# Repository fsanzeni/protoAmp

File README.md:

# 100W USB-C PD Audio Amplifier with Integrated DSP

This repository contains the hardware design files, documentation, and firmware logic for a 100W audio amplifier board. The system integrates USB-C Power Delivery (PD) for power management, a dedicated digital signal processor (DSP) for audio manipulation, a Bluetooth Low Energy (BLE) microcontroller for system management, and a high-efficiency Class-D amplification stage.

This platform is designed for active speaker systems, custom crossover networks, and integrated audio processing applications requiring a compact footprint and standardised power inputs.

| PCB Front | PCB Back |
|-----------|----------|
|  |  |

---

## System Architecture and Major Components

The board design relies on a specialised set of integrated circuits to handle power negotiation, wireless connectivity, digital signal processing, and audio amplification.

### USB Power Delivery: HUSB238

The [HUSB238](https://en.hynetek.com/2421.html) serves as the USB Type-C PD sink controller. It handles the low-level negotiation with the connected USB-C power source to request the necessary voltage and current (up to 20V at 5A, yielding 100W).

* **Protocol:** Compliant with USB PD 3.0 and Type-C 1.4 specifications.
* **Interface:** Interfaced via I2C, allowing the system MCU to read negotiated power capabilities and dynamically limit the amplifier's maximum output power to prevent source overcurrent.
* **Functionality:** Operates independently of the MCU for fundamental power requests, ensuring rapid voltage ramp-up and system stability upon cable insertion. Please note: without writing some code and pushing it via the exposed I2C lines, the HUSB238 can only output a maximum of 20V @ 3A (60W). This is a safety feature. Please see e.g., [Adafruit's](https://github.com/adafruit/Adafruit_HUSB238) code to figure out how to request up to 100W.

### Digital Signal Processor: ADAU1701

Audio processing is handled by the Analog Devices [ADAU1701](https://www.analog.com/en/products/adau1701.html), a fully programmable 28-/56-bit audio DSP.

* **Processing:** Executes audio algorithms at a high sample rate, suitable for bi-quad filters, dynamic range compression, time alignment, and active crossovers.
* **I/O Routing:** Features two built-in ADCs and four DACs, allowing for stereo input and up to four channels of analog output (e.g., routing separate high-frequency and low-frequency channels to the amplification stage).
* **Programming:** Configurable via Analog Devices' SigmaStudio. The DSP boots from an external EEPROM or is initialised via the I2C bus by the system MCU.

### System Controller & Wireless: STM32WBA65

The STMicroelectronics [STM32WBA65CIU6](https://www.st.com/en/microcontrollers-microprocessors/stm32wba65ci.html) acts as the central brain of the board. It is an ultra-low-power Arm Cortex-M33 microcontroller with integrated Bluetooth LE Audio capabilities.

* **System Management:** Acts as the I2C master to configure the HUSB238 (via solder jumpers) and the ADAU1701 (loading DSP parameters or switching presets).
* **Connectivity:** Handles Bluetooth Low Energy (BLE) connections for audio streaming and remote configuration, effectively acting as the bridge between mobile applications and the onboard DSP.

### Audio Amplification Stage

The output stage uses a Class-D amplifier topology configured to deliver up to 100W of total output power, distributed as either a bridged mono (PBTL) output or a standard stereo configuration - or a combination of both.

I'm using here a pair of synced [TPA3126D2DADR](https://www.ti.com/product/TPA3126D2/part-details/TPA3126D2DADR) - one configured as a 50-W stereo amp, the second as a 100-W amp. Obviously you can't request their max wattage at the same time, so I've included a PLIMIT circuit for both. You can also limit the individual amp's power limits via the DSP / SigmaStudio, but better safe than sorry!

---

## License

This project is licensed under the MIT License.

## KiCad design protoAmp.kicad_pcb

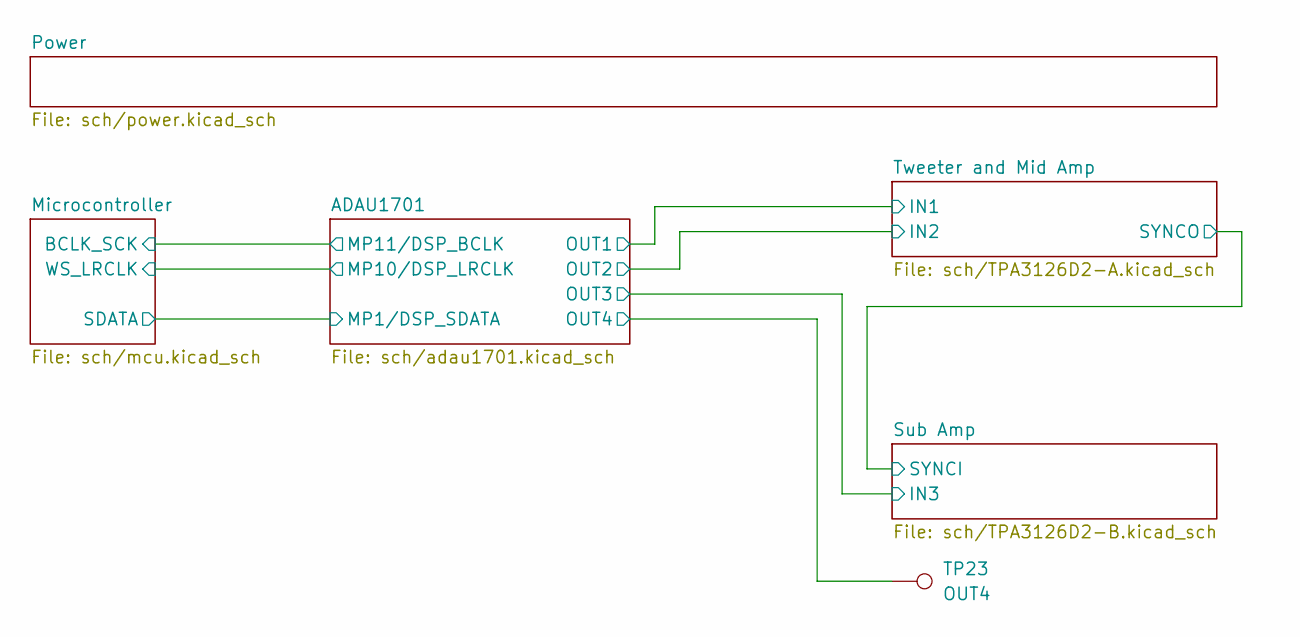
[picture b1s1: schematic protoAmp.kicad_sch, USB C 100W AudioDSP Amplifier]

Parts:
TP23: OUT4; TestPoint_Pad_1.0x1.0mm

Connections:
/ADAU1701/OUT4: TP23.1 (1_1); also elsewhere on the board

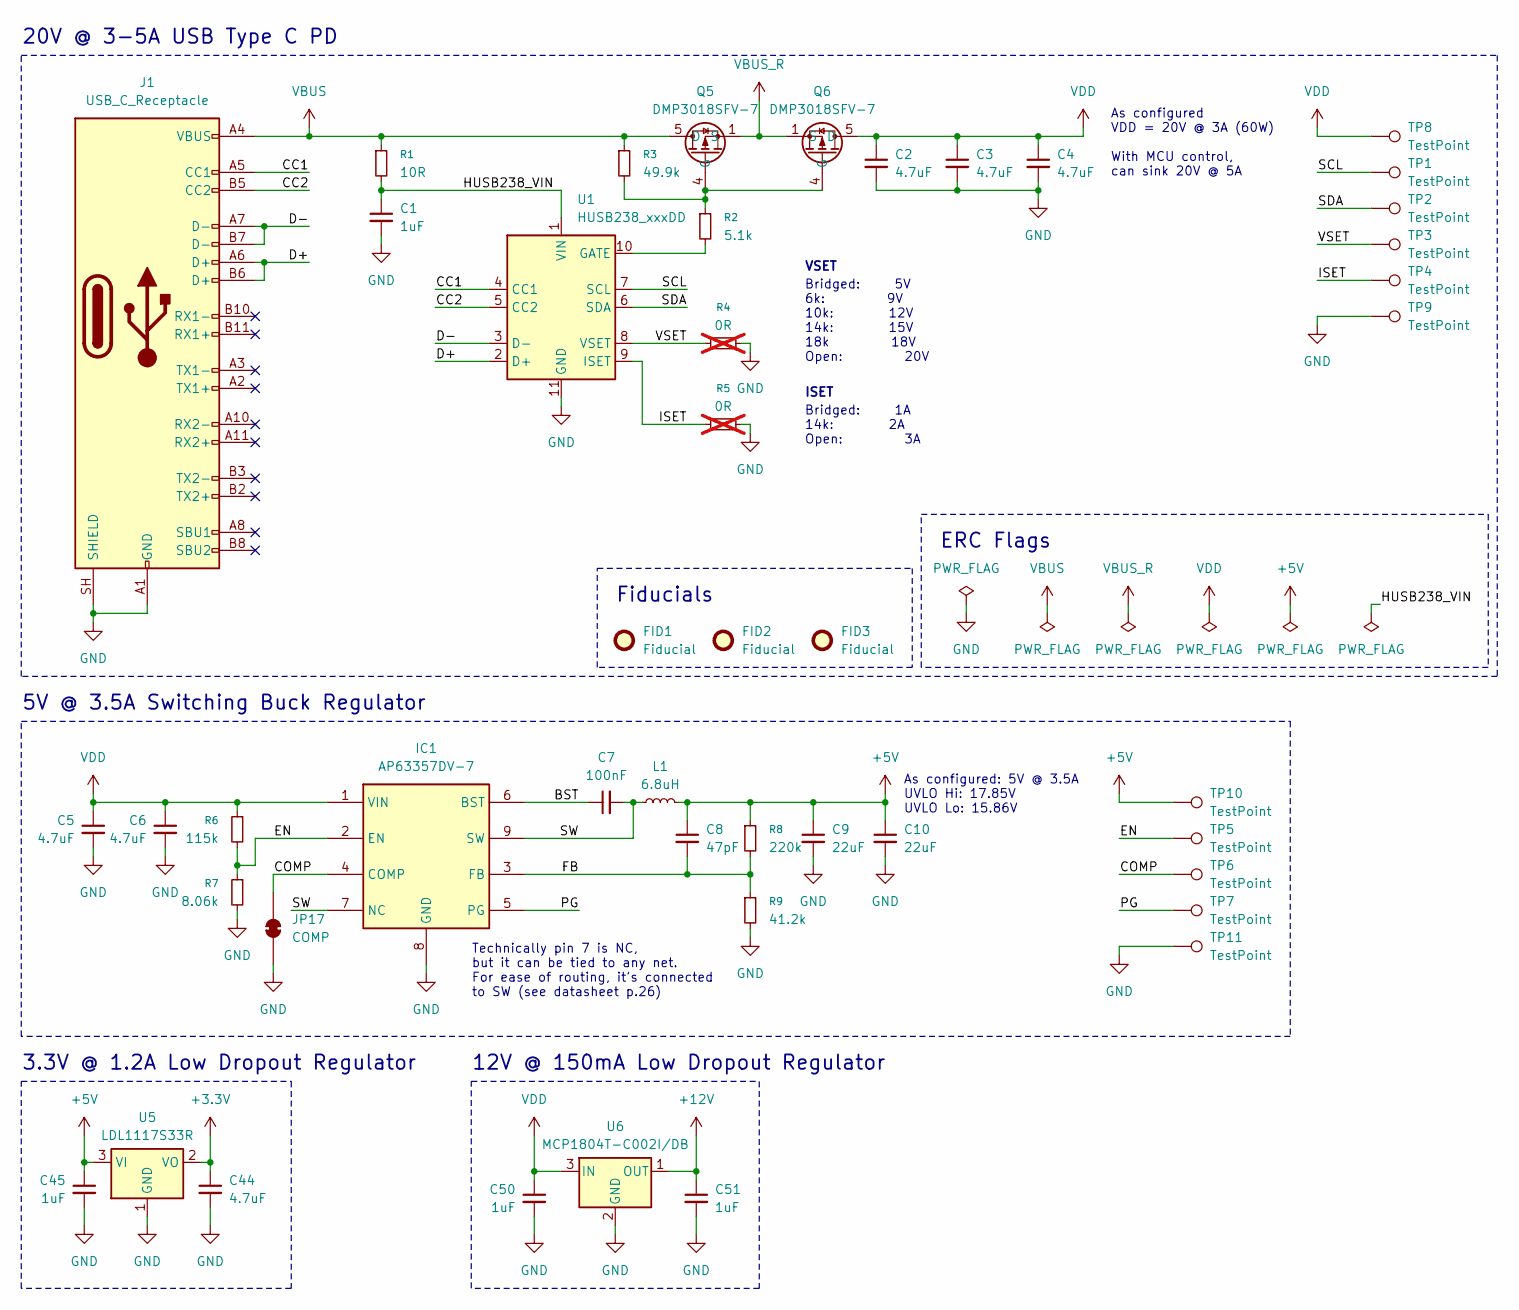
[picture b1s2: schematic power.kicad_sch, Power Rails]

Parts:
C1, C45, C50, C51: 1uF; C_0805_2012Metric
C2, C3, C4, C5, C6, C44: 4.7uF; C_0805_2012Metric
C7: 100nF; C_0402_1005Metric
C8: 47pF; C_0402_1005Metric
C9, C10: 22uF; C_0805_2012Metric
FID1, FID2, FID3: Fiducial; Fiducial_0.75mm_Mask1.5mm
IC1: AP63357DV-7; AP63357DV7; Mouser Part Number 621-AP63357DV-7
J1: USB_C_Receptacle; USB4900-00-A
JP17: COMP; SolderJumper-2_P1.3mm_Bridged_RoundedPad1.0x1.5mm
L1: 6.8uH; SRP1265A-100M
Q5, Q6: DMP3018SFV-7; DMP3036SFV7; Mouser Part Number 621-DMP3018SFV-7
R1: 10R; R_0603_1608Metric
R2: 5.1k; R_0603_1608Metric
R3: 49.9k; R_0603_1608Metric
R4, R5: 0R; R_0603_1608Metric; not fitted
R6: 115k; R_0402_1005Metric
R7: 8.06k; R_0402_1005Metric
R8: 220k; R_0402_1005Metric
R9: 41.2k; R_0402_1005Metric
TP1, TP2, TP3, TP4, TP5, TP6, TP7, TP8, TP9, TP10, TP11: TestPoint; TestPoint_Pad_1.0x1.0mm
U1: HUSB238_xxxDD; WDFN-10-1EP_3x3mm_P0.5mm_EP1.8x2.5mm
U5: LDL1117S33R; SOT-223-3_TabPin2
U6: MCP1804T-C002I/DB; SOT-223-3_TabPin2

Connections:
+3.3V: C44.1, U5.2 (VO); also elsewhere on the board
+5V: C8.1, C9.1, C10.1, C45.1, L1.2, R8.1, TP10.1 (1_1), U5.3 (VI); also elsewhere on the board
+12V: C51.1, U6.1 (OUT); also elsewhere on the board
/Power/BST: C7.1, IC1.6 (BST)
/Power/CC1: J1.A5 (CC1), U1.4 (CC1)
/Power/CC2: J1.B5 (CC2), U1.5 (CC2)
/Power/COMP: IC1.4 (COMP), JP17.1 (A), TP6.1 (1_1)
/Power/D+: J1.A6 (D+), J1.B6 (D+), U1.2 (D+)
/Power/D-: J1.A7 (D-), J1.B7 (D-), U1.3 (D-)
/Power/EN: IC1.2 (EN), R6.2, R7.1, TP5.1 (1_1)
/Power/FB: C8.2, IC1.3 (FB), R8.2, R9.1
/Power/HUSB238_VIN: C1.1, R1.2, U1.1 (VIN)
/Power/ISET: R5.1, TP4.1 (1_1), U1.9 (ISET)
/Power/PG: IC1.5 (PG), TP7.1 (1_1)
/Power/SCL: TP1.1 (1_1), U1.7 (SCL)
/Power/SDA: TP2.1 (1_1), U1.6 (SDA)
/Power/SW: C7.2, IC1.7 (NC), IC1.9 (SW), L1.1
/Power/VSET: R4.1, TP3.1 (1_1), U1.8 (VSET)
GND: C1.2, C2.2, C3.2, C4.2, C5.2, C6.2, C9.2, C10.2, C44.2, C45.2, C50.2, C51.2, IC1.8 (GND), J1.A1 (GND), J1.A12 (GND), J1.B1 (GND), J1.B12 (GND), J1.SH (SHIELD), JP17.2 (B), R4.2, R5.2, R7.2, R9.2, TP9.1 (1_1), TP11.1 (1_1), U1.11 (GND), U5.1 (GND), U6.2 (GND); also elsewhere on the board
unnamed: Q5.4 (G), Q6.4 (G), R2.1, R3.2
unnamed: R2.2, U1.10 (GATE)
VBUS: J1.A4 (VBUS), J1.A9 (VBUS), J1.B4 (VBUS), J1.B9 (VBUS), Q5.5 (D), Q5.6 (D), Q5.7 (D), Q5.8 (D), Q5.9 (D), R1.1, R3.1
VBUS_R: Q5.1 (S), Q5.2 (S), Q5.3 (S), Q6.1 (S), Q6.2 (S), Q6.3 (S)
VDD: C2.1, C3.1, C4.1, C5.1, C6.1, C50.1, IC1.1 (VIN), Q6.5 (D), Q6.6 (D), Q6.7 (D), Q6.8 (D), Q6.9 (D), R6.1, TP8.1 (1_1), U6.3 (IN); also elsewhere on the board

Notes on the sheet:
3.3V @ 1.2A Low Dropout Regulator
Bridged: 1A 14k: 2A Open: 3A
As configured: 5V @ 3.5A UVLO Hi: 17.85V UVLO Lo: 15.86V
Technically pin 7 is NC, but it can be tied to any net. For ease of routing, it's connected to SW (see datasheet p.26)
20V @ 3-5A USB Type C PD
As configured VDD = 20V @ 3A (60W) With MCU control, can sink 20V @ 5A
Fiducials
5V @ 3.5A Switching Buck Regulator
12V @ 150mA Low Dropout Regulator
VSET
Bridged: 5V 6k: 9V 10k: 12V 14k: 15V 18k 18V Open: 20V
ERC Flags
ISET

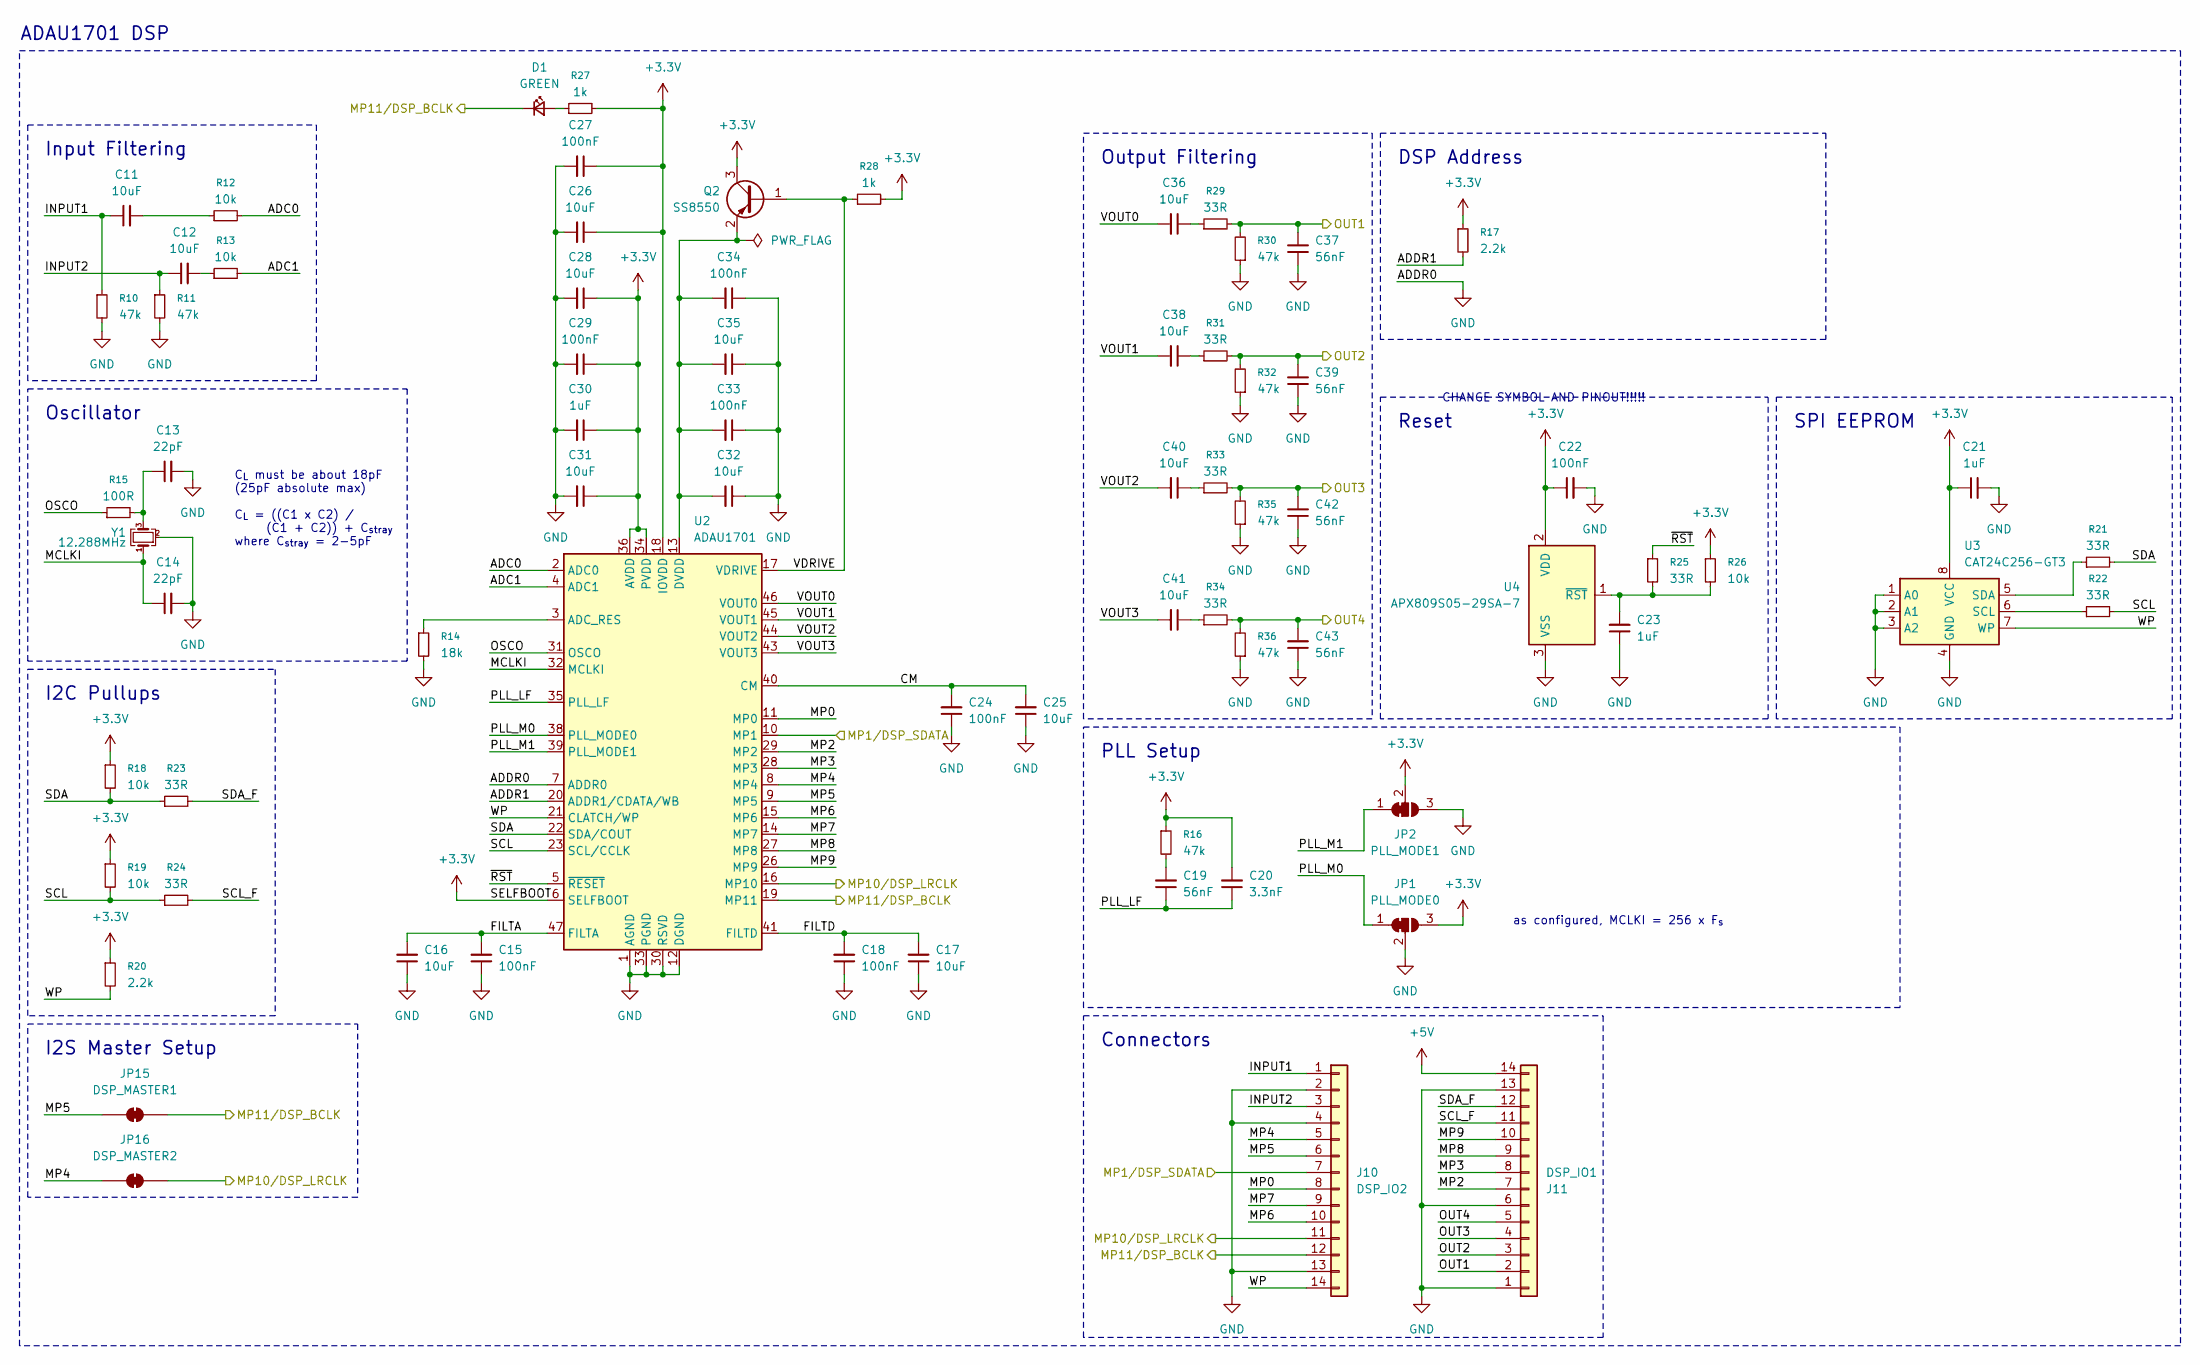
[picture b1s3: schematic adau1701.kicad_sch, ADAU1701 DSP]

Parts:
C11, C12, C16, C17, C25, C26, C28, C31, C32, C35, C36, C38, C40, C41: 10uF; C_0805_2012Metric
C13, C14: 22pF; C_0402_1005Metric
C15, C18, C22, C24, C27, C29, C33, C34: 100nF; C_0402_1005Metric
C19, C37, C39, C42, C43: 56nF; C_0402_1005Metric
C20: 3.3nF; C_0402_1005Metric
C21, C23, C30: 1uF; C_0805_2012Metric
D1: GREEN; LED_0603_1608Metric
J10: DSP_IO2; PinHeader_1x14_P2.54mm_Vertical
J11: DSP_IO1; PinHeader_1x14_P2.54mm_Vertical
JP1: PLL_MODE0; SolderJumper-3_P1.3mm_Bridged12_Pad1.0x1.5mm
JP2: PLL_MODE1; SolderJumper-3_P1.3mm_Bridged12_Pad1.0x1.5mm
JP15: DSP_MASTER1; SolderJumper-2_P1.3mm_Bridged_RoundedPad1.0x1.5mm
JP16: DSP_MASTER2; SolderJumper-2_P1.3mm_Bridged_RoundedPad1.0x1.5mm
Q2: SS8550; SOT-23
R10, R11, R16, R30, R32, R35, R36: 47k; R_0402_1005Metric
R12, R13, R18, R19, R26: 10k; R_0402_1005Metric
R14: 18k; R_0402_1005Metric
R15: 100R; R_0402_1005Metric
R17, R20: 2.2k; R_0402_1005Metric
R21, R22, R23, R24, R25, R29, R31, R33, R34: 33R; R_0402_1005Metric
R27, R28: 1k; R_0402_1005Metric
U2: ADAU1701; LQFP-48_7x7mm_P0.5mm
U3: CAT24C256-GT3; TSSOP-8_4.4x3mm_P0.65mm
U4: APX809S05-29SA-7; SOT-23-3
Y1: 12.288MHz; XTM32012288JT00351001

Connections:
+3.3V: C20.2, C21.1, C22.1, C26.1, C27.1, C28.1, C29.1, C30.1, C31.1, JP1.3 (B), JP2.2 (C), Q2.3 (C), R16.1, R17.1, R18.1, R19.1, R20.1, R26.1, R27.2, R28.2, U2.6 (SELFBOOT), U2.18 (IOVDD), U2.34 (PVDD), U2.36 (AVDD), U2.48 (AVDD), U3.8 (VCC), U4.2 (VDD); also elsewhere on the board
+5V: J11.14; also elsewhere on the board
/ADAU1701/ADC0: R12.2, U2.2 (ADC0)
/ADAU1701/ADC1: R13.2, U2.4 (ADC1)
/ADAU1701/ADDR1: R17.2, U2.20 (ADDR1/CDATA/WB)
/ADAU1701/CM: C24.2, C25.2, U2.40 (CM)
/ADAU1701/FILTA: C15.2, C16.2, U2.47 (FILTA)
/ADAU1701/FILTD: C17.2, C18.2, U2.41 (FILTD)
/ADAU1701/INPUT1: C11.1, J10.1, R10.1
/ADAU1701/INPUT2: C12.1, J10.3, R11.1
/ADAU1701/MCLKI: C14.1, U2.32 (MCLKI), Y1.1
/ADAU1701/MP0: J10.8, U2.11 (MP0)
/ADAU1701/MP1/DSP_SDATA: J10.7, U2.10 (MP1); also elsewhere on the board
/ADAU1701/MP2: J11.7, U2.29 (MP2)
/ADAU1701/MP3: J11.8, U2.28 (MP3)
/ADAU1701/MP4: J10.5, JP16.2 (B), U2.8 (MP4)
/ADAU1701/MP5: J10.6, JP15.2 (B), U2.9 (MP5)
/ADAU1701/MP6: J10.10, U2.15 (MP6)
/ADAU1701/MP7: J10.9, U2.14 (MP7)
/ADAU1701/MP8: J11.9, U2.27 (MP8)
/ADAU1701/MP9: J11.10, U2.26 (MP9)
/ADAU1701/MP10/DSP_LRCLK: J10.11, JP16.1 (A), U2.16 (MP10); also elsewhere on the board
/ADAU1701/MP11/DSP_BCLK: D1.1 (K), J10.12, JP15.1 (A), U2.19 (MP11); also elsewhere on the board
/ADAU1701/OSCO: R15.1, U2.31 (OSCO)
/ADAU1701/OUT1: C37.2, J11.2, R29.2, R30.2; also elsewhere on the board
/ADAU1701/OUT2: C39.2, J11.3, R31.2, R32.2; also elsewhere on the board
/ADAU1701/OUT3: C42.2, J11.4, R33.2, R35.2; also elsewhere on the board
/ADAU1701/OUT4: C43.2, J11.5, R34.2, R36.2; also elsewhere on the board
/ADAU1701/PLL_LF: C19.1, C20.1, U2.35 (PLL_LF)
/ADAU1701/PLL_M0: JP1.1 (A), U2.38 (PLL_MODE0)
/ADAU1701/PLL_M1: JP2.1 (A), U2.39 (PLL_MODE1)
/ADAU1701/SCL: R19.2, R22.2, R24.1, U2.23 (SCL/CCLK)
/ADAU1701/SCL_F: J11.11, R24.2
/ADAU1701/SDA: R18.2, R21.2, R23.1, U2.22 (SDA/COUT)
/ADAU1701/SDA_F: J11.12, R23.2
/ADAU1701/VDRIVE: Q2.1 (B), R28.1, U2.17 (VDRIVE)
/ADAU1701/VOUT0: C36.2, U2.46 (VOUT0)
/ADAU1701/VOUT1: C38.2, U2.45 (VOUT1)
/ADAU1701/VOUT2: C40.2, U2.44 (VOUT2)
/ADAU1701/VOUT3: C41.2, U2.43 (VOUT3)
/ADAU1701/WP: J10.14, R20.2, U2.21 (CLATCH/WP), U3.7 (WP)
/ADAU1701/~RST: R25.1, U2.5 (~RESET)
GND: C13.2, C14.2, C15.1, C16.1, C17.1, C18.1, C21.2, C22.2, C23.1, C24.1, C25.1, C26.2, C27.2, C28.2, C29.2, C30.2, C31.2, C32.1, C33.1, C34.1, C35.1, C37.1, C39.1, C42.1, C43.1, J10.2, J10.4, J10.13, J11.1, J11.6, J11.13, JP1.2 (C), JP2.3 (B), R10.2, R11.2, R14.2, R30.1, R32.1, R35.1, R36.1, U2.1 (AGND), U2.7 (ADDR0), U2.12 (DGND), U2.25 (DGND), U2.30 (RSVD), U2.33 (PGND), U2.37 (AGND), U2.42 (AGND), U3.1 (A0), U3.2 (A1), U3.3 (A2), U3.4 (GND), U4.3 (VSS), Y1.2 (G), Y1.4 (G); also elsewhere on the board
unnamed: C11.2, R12.1
unnamed: C12.2, R13.1
unnamed: C13.1, R15.2, Y1.3
unnamed: C19.2, R16.2
unnamed: C36.1, R29.1
unnamed: C38.1, R31.1
unnamed: C40.1, R33.1
unnamed: C41.1, R34.1
unnamed: D1.2 (A), R27.1
unnamed: C32.2, C33.2, C34.2, C35.2, Q2.2 (E), U2.13 (DVDD), U2.24 (DVDD)
unnamed: R14.1, U2.3 (ADC_RES)
unnamed: R22.1, U3.6 (SCL)
unnamed: R21.1, U3.5 (SDA)
unnamed: C23.2, R25.2, R26.2, U4.1 (~RST)

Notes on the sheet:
Reset
C_{L} must be about 18pF (25pF absolute max) C_{L} = ((C1 x C2) / (C1 + C2)) + C_{stray} where C_{stray} = 2-5pF
Output Filtering
PLL Setup
ADAU1701 DSP
Input Filtering
I2S Master Setup
SPI EEPROM
Oscillator
I2C Pullups
as configured, MCLKI = 256 x F_{s}
DSP Address
CHANGE SYMBOL AND PINOUT!!!!!
Connectors

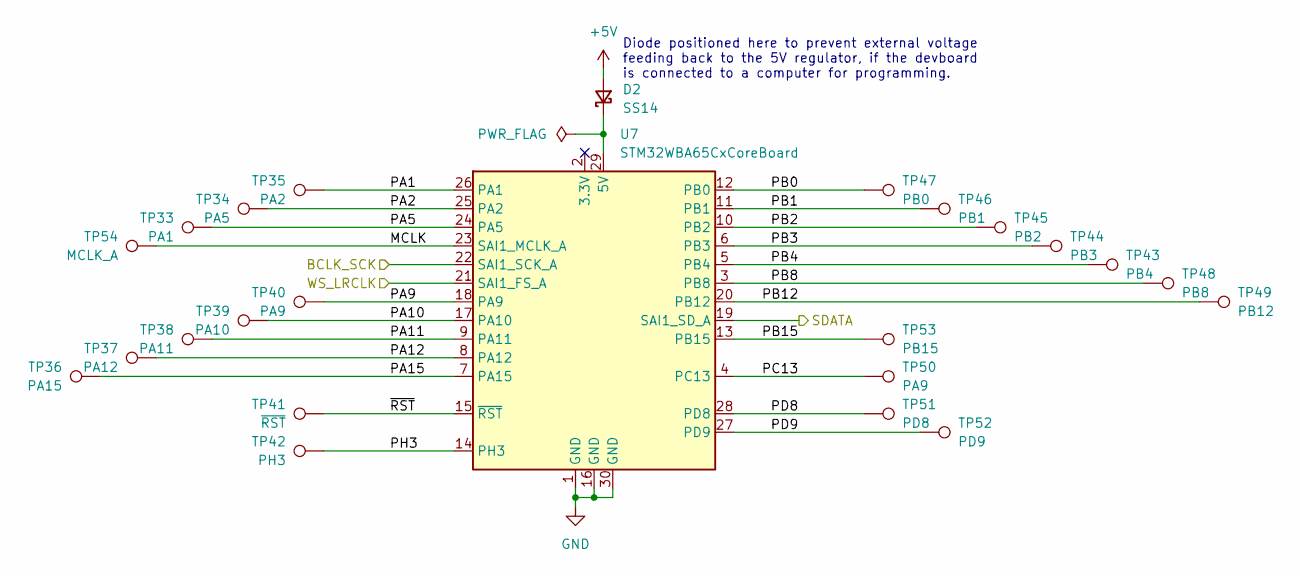
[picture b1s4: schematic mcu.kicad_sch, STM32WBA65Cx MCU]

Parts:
D2: SS14; D_SMA
TP33: PA1; TestPoint_THTPad_1.0x1.0mm_Drill0.5mm
TP34: PA5; TestPoint_THTPad_1.0x1.0mm_Drill0.5mm
TP35: PA2; TestPoint_THTPad_1.0x1.0mm_Drill0.5mm
TP36: PA15; TestPoint_THTPad_1.0x1.0mm_Drill0.5mm
TP37: PA12; TestPoint_THTPad_1.0x1.0mm_Drill0.5mm
TP38: PA11; TestPoint_THTPad_1.0x1.0mm_Drill0.5mm
TP39: PA10; TestPoint_THTPad_1.0x1.0mm_Drill0.5mm
TP40, TP50: PA9; TestPoint_THTPad_1.0x1.0mm_Drill0.5mm
TP41: ~{RST}; TestPoint_THTPad_1.0x1.0mm_Drill0.5mm
TP42: PH3; TestPoint_THTPad_1.0x1.0mm_Drill0.5mm
TP43: PB4; TestPoint_THTPad_1.0x1.0mm_Drill0.5mm
TP44: PB3; TestPoint_THTPad_1.0x1.0mm_Drill0.5mm
TP45: PB2; TestPoint_THTPad_1.0x1.0mm_Drill0.5mm
TP46: PB1; TestPoint_THTPad_1.0x1.0mm_Drill0.5mm
TP47: PB0; TestPoint_THTPad_1.0x1.0mm_Drill0.5mm
TP48: PB8; TestPoint_THTPad_1.0x1.0mm_Drill0.5mm
TP49: PB12; TestPoint_THTPad_1.0x1.0mm_Drill0.5mm
TP51: PD8; TestPoint_THTPad_1.0x1.0mm_Drill0.5mm
TP52: PD9; TestPoint_THTPad_1.0x1.0mm_Drill0.5mm
TP53: PB15; TestPoint_THTPad_1.0x1.0mm_Drill0.5mm
TP54: MCLK_A; TestPoint_THTPad_1.0x1.0mm_Drill0.5mm
U7: STM32WBA65CxCoreBoard; WeAct STM32WBA65CIU6

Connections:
+5V: D2.2 (A); also elsewhere on the board
/ADAU1701/MP1/DSP_SDATA: U7.19 (SAI1_SD_A); also elsewhere on the board
/ADAU1701/MP10/DSP_LRCLK: U7.21 (SAI1_FS_A); also elsewhere on the board
/ADAU1701/MP11/DSP_BCLK: U7.22 (SAI1_SCK_A); also elsewhere on the board
/Microcontroller/MCLK: TP54.1 (1_1), U7.23 (SAI1_MCLK_A)
/Microcontroller/PA1: TP35.1 (1_1), U7.26 (PA1)
/Microcontroller/PA2: TP34.1 (1_1), U7.25 (PA2)
/Microcontroller/PA5: TP33.1 (1_1), U7.24 (PA5)
/Microcontroller/PA9: TP40.1 (1_1), U7.18 (PA9)
/Microcontroller/PA10: TP39.1 (1_1), U7.17 (PA10)
/Microcontroller/PA11: TP38.1 (1_1), U7.9 (PA11)
/Microcontroller/PA12: TP37.1 (1_1), U7.8 (PA12)
/Microcontroller/PA15: TP36.1 (1_1), U7.7 (PA15)
/Microcontroller/PB0: TP47.1 (1_1), U7.12 (PB0)
/Microcontroller/PB1: TP46.1 (1_1), U7.11 (PB1)
/Microcontroller/PB2: TP45.1 (1_1), U7.10 (PB2)
/Microcontroller/PB3: TP44.1 (1_1), U7.6 (PB3)
/Microcontroller/PB4: TP43.1 (1_1), U7.5 (PB4)
/Microcontroller/PB8: TP48.1 (1_1), U7.3 (PB8)
/Microcontroller/PB12: TP49.1 (1_1), U7.20 (PB12)
/Microcontroller/PB15: TP53.1 (1_1), U7.13 (PB15)
/Microcontroller/PC13: TP50.1 (1_1), U7.4 (PC13)
/Microcontroller/PD8: TP51.1 (1_1), U7.28 (PD8)
/Microcontroller/PD9: TP52.1 (1_1), U7.27 (PD9)
/Microcontroller/PH3: TP42.1 (1_1), U7.14 (PH3)
/Microcontroller/~RST: TP41.1 (1_1), U7.15 (~RST)
GND: U7.1 (GND), U7.16 (GND), U7.30 (GND); also elsewhere on the board
unnamed: D2.1 (K), U7.29 (5V)

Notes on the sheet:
Diode positioned here to prevent external voltage feeding back to the 5V regulator, if the devboard is connected to a computer for programming.

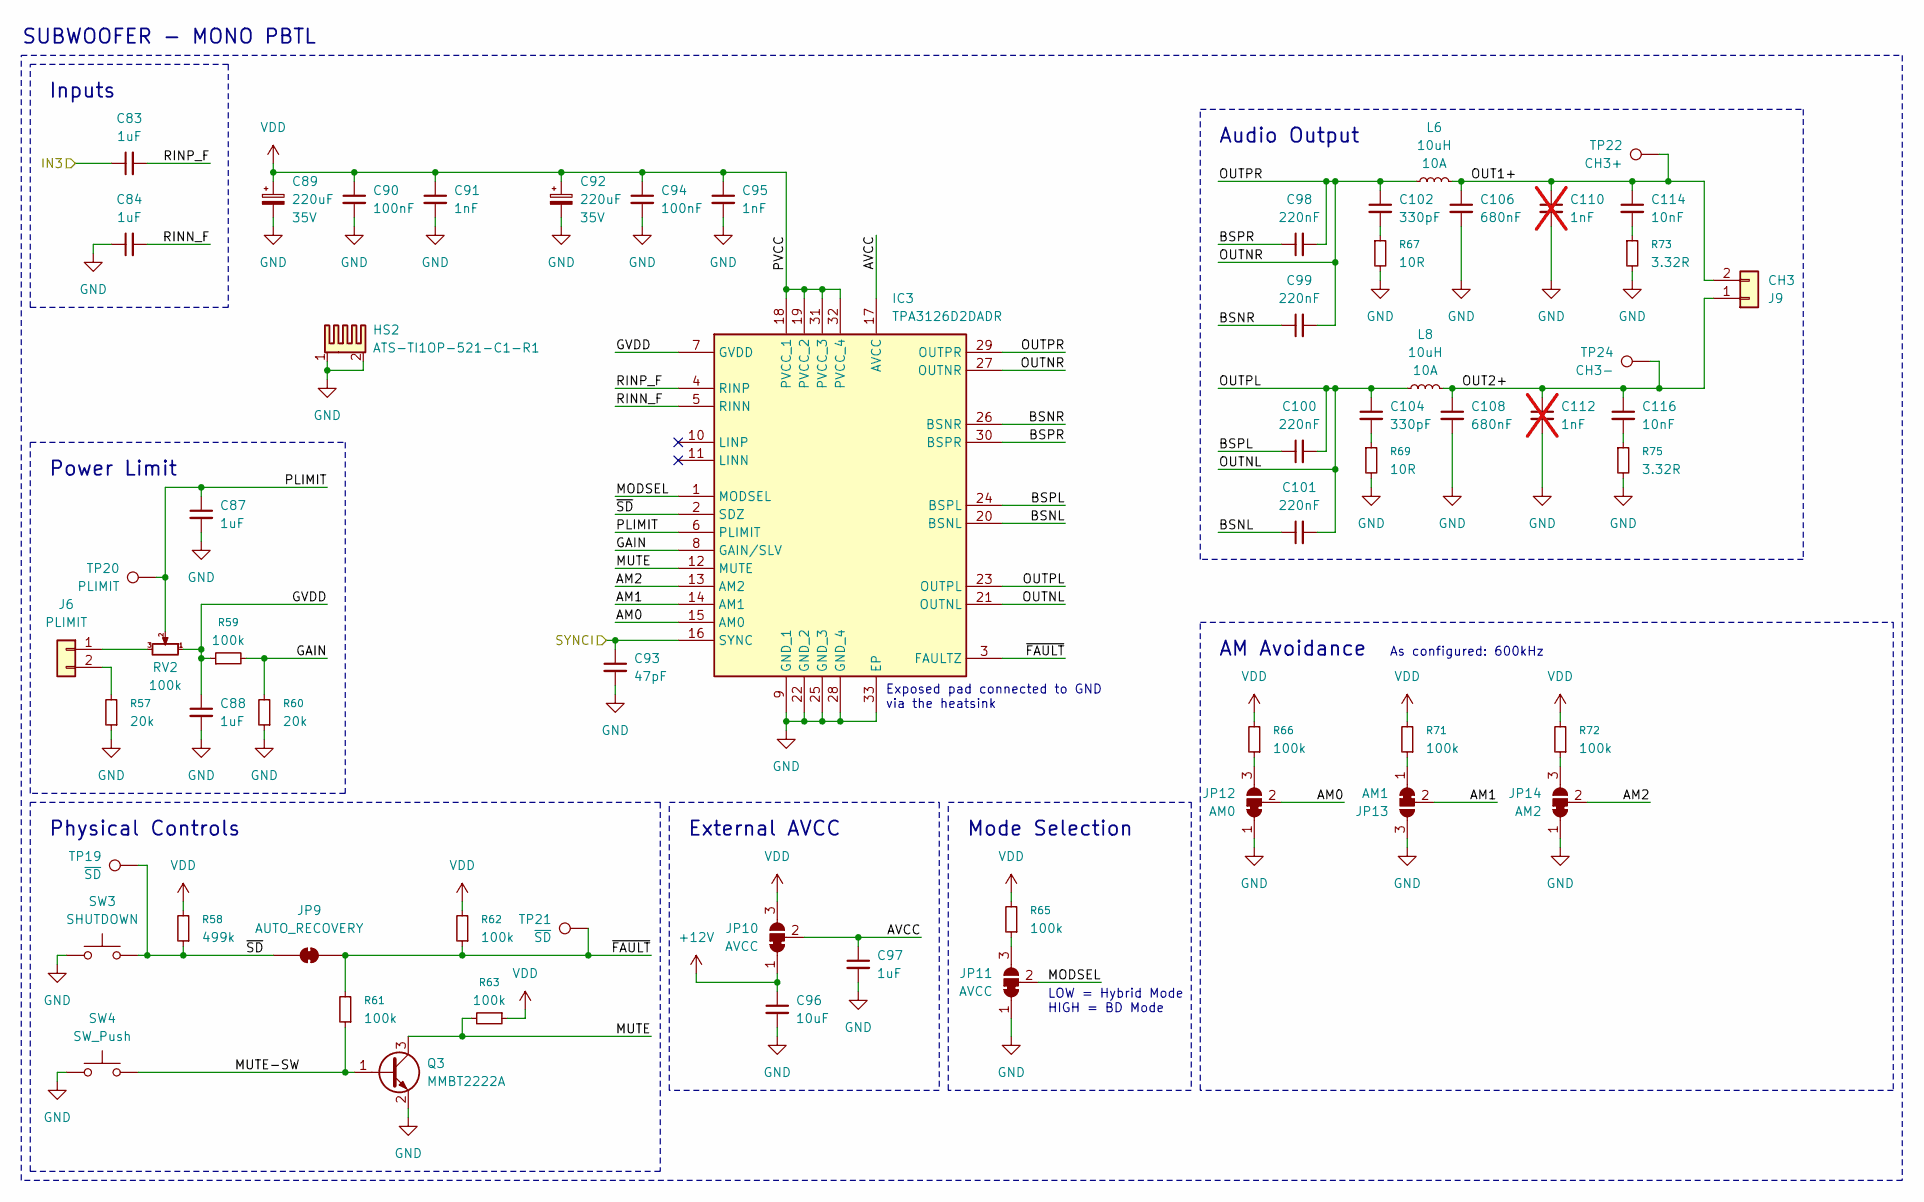
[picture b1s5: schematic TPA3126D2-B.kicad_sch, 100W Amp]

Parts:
C83, C84, C97: 1uF; C_0603_1608Metric
C87, C88: 1uF; C_0805_2012Metric
C89, C92: 220uF; CP_Radial_D10.0mm_P5.00mm; Rating 35V
C90, C94: 100nF; C_0603_1608Metric
C91, C95: 1nF; C_0603_1608Metric
C93: 47pF; C_0603_1608Metric
C96: 10uF; C_1210_3225Metric
C98, C99, C100, C101: 220nF; C_0603_1608Metric
C102, C104: 330pF; C_0603_1608Metric
C106, C108: 680nF; C_1206_3216Metric
C110, C112: 1nF; C_0603_1608Metric; not fitted
C114, C116: 10nF; C_0603_1608Metric
HS2: ATS-TI1OP-521-C1-R1
IC3: TPA3126D2DADR; SOP65P810X120-33N; Mouser Part Number 595-TPA3126D2DADR
J6: PLIMIT; PinHeader_1x02_P2.54mm_Vertical
J9: CH3; TerminalBlock_Xinya_XY308-2.54-2P_1x02_P2.54mm_Horizontal
JP9: AUTO_RECOVERY; SolderJumper-2_P1.3mm_Bridged_RoundedPad1.0x1.5mm
JP10, JP11: AVCC; SolderJumper-3_P1.3mm_Bridged12_Pad1.0x1.5mm
JP12: AM0; SolderJumper-3_P1.3mm_Bridged12_Pad1.0x1.5mm
JP13: AM1; SolderJumper-3_P1.3mm_Bridged12_Pad1.0x1.5mm
JP14: AM2; SolderJumper-3_P1.3mm_Bridged12_Pad1.0x1.5mm
L6, L8: 10uH; SRP1265A-100M; Rating 10A
Q3: MMBT2222A; SOT-23
R57, R60: 20k; R_0805_2012Metric
R58: 499k; R_0603_1608Metric
R59: 100k; R_0805_2012Metric
R61, R62, R63, R65, R66, R71, R72: 100k; R_0603_1608Metric
R67, R69: 10R; R_0805_2012Metric
R73, R75: 3.32R; R_0603_1608Metric
RV2: 100k; Potentiometer_Bourns_3386P_Vertical
SW3: SHUTDOWN; SW_PUSH_6mm
SW4: SW_Push; SW_PUSH_6mm
TP19, TP21: ~{SD}; TestPoint_Pad_1.0x1.0mm
TP20: PLIMIT; TestPoint_Pad_1.0x1.0mm
TP22: CH3+; TestPoint_Pad_1.0x1.0mm
TP24: CH3-; TestPoint_Pad_1.0x1.0mm

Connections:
+12V: C96.1, JP10.1 (A); also elsewhere on the board
/ADAU1701/OUT3: C83.1; also elsewhere on the board
/Sub Amp/AM0: IC3.15 (AM0), JP12.2 (C)
/Sub Amp/AM1: IC3.14 (AM1), JP13.2 (C)
/Sub Amp/AM2: IC3.13 (AM2), JP14.2 (C)
/Sub Amp/AVCC: C97.1, IC3.17 (AVCC), JP10.2 (C)
/Sub Amp/BSNL: C101.1, IC3.20 (BSNL)
/Sub Amp/BSNR: C99.1, IC3.26 (BSNR)
/Sub Amp/BSPL: C100.1, IC3.24 (BSPL)
/Sub Amp/BSPR: C98.1, IC3.30 (BSPR)
/Sub Amp/GAIN: IC3.8 (GAIN/SLV), R59.2, R60.2
/Sub Amp/GVDD: C88.1, IC3.7 (GVDD), R59.1, RV2.1
/Sub Amp/MODSEL: IC3.1 (MODSEL), JP11.2 (C)
/Sub Amp/MUTE: IC3.12 (MUTE), Q3.3 (C), R63.2
/Sub Amp/MUTE-SW: Q3.1 (B), R61.1, SW4.2
/Sub Amp/OUT1+: C106.1, C110.1, C114.1, J9.2, L6.2, TP22.1 (1_1)
/Sub Amp/OUT2+: C108.1, C112.1, C116.1, J9.1, L8.2, TP24.1 (1_1)
/Sub Amp/OUTNL: C100.2, C101.2, C104.1, IC3.21 (OUTNL), IC3.23 (OUTPL), L8.1
/Sub Amp/OUTNR: C98.2, C99.2, C102.1, IC3.27 (OUTNR), IC3.29 (OUTPR), L6.1
/Sub Amp/PLIMIT: C87.1, IC3.6 (PLIMIT), RV2.2, TP20.1 (1_1)
/Sub Amp/RINN_F: C84.2, IC3.5 (RINN)
/Sub Amp/RINP_F: C83.2, IC3.4 (RINP)
/Sub Amp/SYNCI: C93.1, IC3.16 (SYNC); also elsewhere on the board
/Sub Amp/~FAULT: IC3.3 (FAULTZ), JP9.2 (B), R61.2, R62.1, TP21.1 (1_1)
/Sub Amp/~SD: IC3.2 (SDZ), JP9.1 (A), R58.1, SW3.2, TP19.1 (1_1)
GND: C84.1, C87.2, C88.2, C89.2, C90.2, C91.2, C92.2, C93.2, C94.2, C95.2, C96.2, C97.2, C106.2, C108.2, C110.2, C112.2, HS2.1, HS2.2, IC3.9 (GND_1), IC3.22 (GND_2), IC3.25 (GND_3), IC3.28 (GND_4), IC3.33 (EP), JP11.1 (A), JP12.1 (A), JP13.3 (B), JP14.1 (A), Q3.2 (E), R57.1, R60.1, R67.2, R69.2, R73.2, R75.2, SW3.1, SW4.1; also elsewhere on the board
unnamed: C102.2, R67.1
unnamed: C104.2, R69.1
unnamed: C114.2, R73.1
unnamed: C116.2, R75.1
unnamed: J6.1, RV2.3
unnamed: J6.2, R57.2
unnamed: JP11.3 (B), R65.1
unnamed: JP12.3 (B), R66.1
unnamed: JP13.1 (A), R71.1
unnamed: JP14.3 (B), R72.1
VDD: C89.1, C90.1, C91.1, C92.1, C94.1, C95.1, IC3.18 (PVCC_1), IC3.19 (PVCC_2), IC3.31 (PVCC_3), IC3.32 (PVCC_4), JP10.3 (B), R58.2, R62.2, R63.1, R65.2, R66.2, R71.2, R72.2; also elsewhere on the board

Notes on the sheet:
Audio Output
External AVCC
SUBWOOFER - MONO PBTL
Power Limit
As configured: 600kHz
Inputs
Physical Controls
LOW = Hybrid Mode HIGH = BD Mode
AM Avoidance
Exposed pad connected to GND via the heatsink
Mode Selection
